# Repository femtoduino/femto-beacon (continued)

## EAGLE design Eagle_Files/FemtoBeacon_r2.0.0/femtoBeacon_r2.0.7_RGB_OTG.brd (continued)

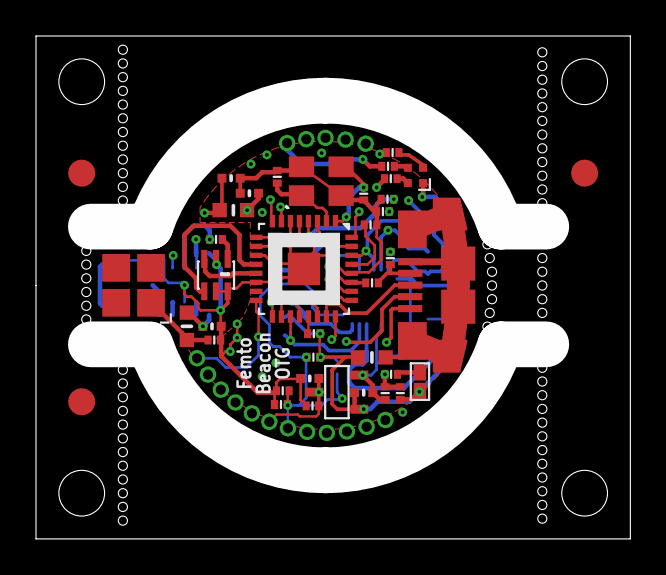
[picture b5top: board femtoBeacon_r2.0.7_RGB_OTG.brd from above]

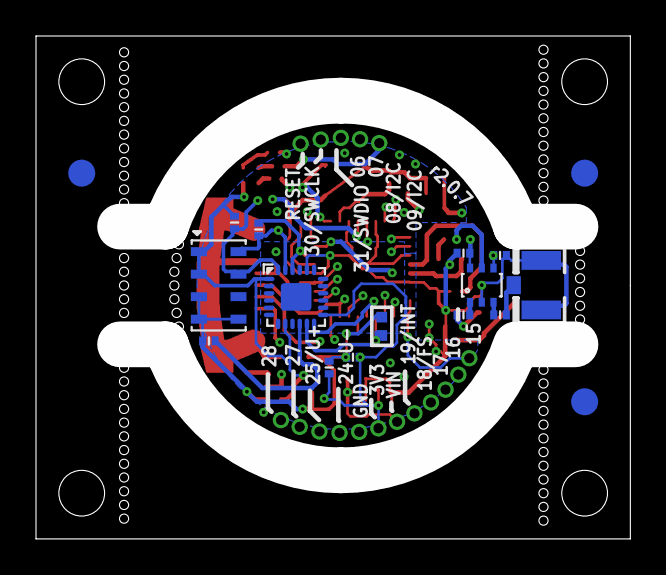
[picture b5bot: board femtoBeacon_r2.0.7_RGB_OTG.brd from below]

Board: 4 copper layers, 33.0 x 27.9 mm, 73 parts (17 on the bottom side), 41 nets.

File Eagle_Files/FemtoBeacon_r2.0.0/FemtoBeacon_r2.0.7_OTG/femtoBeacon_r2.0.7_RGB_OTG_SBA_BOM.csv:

##########################################################################
       Name: Placement Bill of Materials Generator

    Version: 4 (2-sided, top)
         By: Small Batch Assembly
        URL: www.smallbatchassembly.com
 SourceFile: femtoBeacon_r2.0.7_RGB_OTG.brd
   DateTime: 11/24/17 7:52 PM
      Units: inches
##########################################################################
REF,PACKAGE,VALUE,X,Y,ROTATION,
ANT_SMD   , 0479480001            , 0479480001     , 0.2137, 0.5543, 180.0
BALUN   , 0805_BALUN            , JOHANSON_2450BM15A0015E     , 0.3937, 0.5770, 270.0
BTN   , SPST_SMD            , DNP     , 0.8398, 0.3440, 270.0
C1   , PART            , 0.1uF     , 0.7968, 0.3190, 270.0
C2   , PART            , 0.1uF     , 0.6077, 0.4490, 0.0
C5   , _0402MP            , 2.2uF     , 0.7167, 0.3200, 180.0
C6   , _0402MP            , 2.2uF     , 0.5987, 0.3510, 180.0
C7   , PART            , 0.47uF     , 0.6047, 0.2910, 180.0
C8   , PART            , 0.1uF     , 0.7687, 0.7430, 180.0
C9   , PART            , 0.1uF     , 0.7318, 0.6870, 0.0
C10   , PART            , 0.1uF     , 0.5397, 0.3240, 180.0
C11   , _0402MP            , 1.2pF     , 0.3850, 0.4650, 0.0
C12   , PART            , 22pF     , 0.3937, 0.6550, 180.0
C13   , PART            , DNP     , 0.3900, 0.4350, 0.0
C14   , PART            , 9pF     , 0.5277, 0.7920, 270.0
C15   , PART            , 9pF     , 0.7167, 0.7550, 270.0
C16   , PART            , 0.1uF     , 0.6067, 0.3975, 0.0
C17   , PART            , 0.1uF     , 0.7587, 0.7160, 180.0
C21   , _0402MP            , 10uF     , 0.4267, 0.7890, 180.0
C22   , _0402MP            , 10uF     , 0.4667, 0.7560, 0.0
C31   , PART            , 10nF     , 0.5357, 0.2940, 0.0
FB1   , _0603MP            , Ferrite     , 0.7347, 0.3970, 180.0
FID1   , FIDUCIAL_1MM            , FIDUCIAL     , 0.1000, 0.3000, 0.0
FID2   , FIDUCIAL_1MM            , FIDUCIAL     , 0.1000, 0.8000, 0.0
FID3   , FIDUCIAL_1MM            , FIDUCIAL     , 1.2000, 0.8000, 0.0
IC   , QFN32            , ATSAMR21E18A-MUT     , 0.5861, 0.5907, 270.0
L1   , _0603MP            , 1.8nH     , 0.3300, 0.4650, 270.0
L6   , _0603MP            , 10uH     , 0.4317, 0.7190, 0.0
LDO_VREG   , MCP1700T-3302E/TT            , MCP1700T-3302E/TT     , 0.6581, 0.3211, 90.0
R1   , PART            , 330     , 0.7767, 0.3600, 180.0
R2   , PART            , 10K     , 0.7637, 0.3190, 270.0
R4   , PART            , 330     , 0.7760, 0.7880, 0.0
R5   , PART            , 330     , 0.7350, 0.5600, 0.0
R6   , PART            , 330     , 0.7700, 0.8150, 0.0
R7   , PART            , 330     , 0.7800, 0.8450, 0.0
R10   , PART            , 100K     , 0.7750, 0.6140, 90.0
RGBLED   , LRTB_R48G            , LRTB_R48G     , 0.8300, 0.7950, 270.0
USB   , USB_MICROB_PACKAGE            , USB_MICROB     , 0.8764, 0.5550, 90.0
XOSCRF   , TSX-3225            , 16MHz     , 0.6240, 0.7825, 0.0

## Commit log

2015-04-29 MPU9250 library should be a submodule...
2015-04-29 Adding FemtoIO MPU9250 git repo as submodule in the libraries folder
2015-05-09 Initial work on the FemtoBeacon board configs, and examples with IMU
2015-05-17 Cleaning up, adding sam-r21-imu example work
2015-05-17 More clean up. Renamed the blink example to a more appropriate name
2015-05-17 Adding in EAGLE PCB board design files, modifying the blink example
2015-05-17 Moving the sam-r21-blinky folder to sam-r21-blink
2015-05-17 Adding the blink example back in
2015-05-17 Updating examples, and renaming openocd config files accordingly
2015-05-18 Cleaning up the sam-r21-blink example
2015-05-18 Minor update to the gitignore file
2015-05-24 Adding in FemtoBeacon Dongle (SAM R21 w/ Antenna, no IMU and barometer)
2015-06-10 Minor update to Fabrication notes and parts list
2016-03-18 Committing current work on FemtoBeacon (zigbee/mesh) r2.0.1, and USB dongle
2016-03-22 Updating femtoBeacon dongle r2.0.1
2017-01-18 Updating README
2017-11-17 Revision 2.0.7 of the coin, with USB Host and RGB LED, plus u.FL connector
2017-11-17 Adding Blender 3D case model
2018-01-04 Adding FemtoBeacon coin r2.0.7, and FemtoBeacon dongle r2.0.6
2018-01-04 A ton of work.
2018-01-05 Adding dimension data to FemtoBeacon coin r2.0.7, adding stencil and PCB jig model (Blender 3D and STL file for Cura)
2018-01-05 Minor update to Blender 3D file
2018-01-12 Adding initial Taiyo Yuden BT5 module based FemtoBeacon revision 2.0.0 design, adding FemtoBeacon Dongle r2.0.6 solder paste/stencil jig (Blender 3D, Cura slice) and FemtoBeacon coin r2.0.7 solder pa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
2018-01-12 Minor update to the Blender 3D modle of femtoBeacon dongle r2.05 solder paste stencil jig
2018-01-12 Adding in new Cura files for the solder paste stencil jigs
2018-01-12 Updating the femtoBeacon dongle r2.0.6 solder paste jig
2018-01-12 Adjusting Cura slice to improve first layer 3D print
2018-08-14 Updating 3D printable case and lids for FemtoBeacon r2.0.7
2019-04-08 Current work on ESP32 based designs
2019-04-09 Adding dims to ESP32 based board
2019-04-10 Updating ESP32-WROOM-32 board. RGB Blue pin reassigned, and RGB pin 1 set to VCC instead of GND. LiPo connector pins were switched, corrected now.
2019-04-18 Fixing solder stop mask on femto-beacon-esp32coin and femto-beacon-esp32-lps. Adding Blender3D model of stencil jig for the coin
2019-04-19 Setting correct ESP32 chip for the coin design to ESP32‑D2WD as it has 2MiB of internal Flash
2019-04-20 Adding new ESP32-PICO-D4 based coin with IMU and altimeter
2019-04-23 Adding FemtoBeacon ESP32 LPS board with ESP32-PICO-D4 chip
2019-05-18 Current work on Hacker House board, and ESP32 coins
2019-06-14 Adding FemtoBeacon ESP32-D2WD Product Brochure
2019-06-25 Setting Serial baud rate to 9600 instead of 115200 to prevent brown out detection triggering
2019-06-25 Nope, back to 115200.
2019-08-10 Revised BoM for the Hacker.House board, fixed missing 3V3 trace with 2.0.1 design of Hacker.House board (version bump to 2.0.2)
2019-08-10 Updating BoM for Hacker.House board. Using ESP32-WROOM-32D (16MB) variant
2020-05-26 Adding MicroPython examples and library
